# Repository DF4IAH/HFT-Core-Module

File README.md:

# HFT-Core-Module

## V1.1 PCB after placement was done:

## These are the included devices for the V1.1:
* __CPU: ST Microelectronics STM32L496ZGT6P__ (80MHz ARM Cortex-M4 w/ 1MB FLASH / 320kB RAM)
* __ext. Flash and EEPROM__ (8MB more data to be kept outside of the MCU / 8kB configuration data)
* __GSM / GNSS / BT: SIM868__ (SMS / GPRS / GPS, Glonass ...)
* __VHF/UHF FSK and LoRa: SX1262__ (VHF TX/RX)
* __VHF/UHF All but Lora: AX5243__ (VHF TX/RX)
* __Accel/Gyro/Mag: BNO085__ (3Axis-Acceleration, 3Axis-Gyro, 3Axis-Magneto - motion tracking engine)
* __Baro/Hygro/Temp/AirQuality: BME680__ (0.12Pa equiv. 1.7cm)
* __VCTCXO: CFPT-141_20MHz__ (being synchronized to the GPS 1PPS signal by pulling the VC)
* __Clock PLL__ (distributing any clocks that are needed)
* __Audio ADC and DAC__ (connected to the I2S facilities)
* __LCD 16x2 display__ (draws less than 1mA from the battery)
* __E-Ink-Display w/ 200x200px__ (more fun with even less energy)
* __Rotary encoder w/ pushbutton__ (Navigation of menues enabled)
* __Archer Headers__ (PCB expanded by up to two daughter boards)
* __SMA sockets: GSM, GNSS, BlueTooth, SX1262, AX5243__ (each device has its own antenna socket)
* __PMICs for 12V, USB, solar cells, 3.3V, 1.2V__ (high efficiency on board)
* __Electronic Switches: Subcircuits to be powered on/off by request__ (ultra-low-power to full-media)
* __LiPo-Connector: 1-cell 3.7V__ (high power request by the SIM868 device to be satisfied)
* __... and much fun with Free-RTOS...__ (Efficiency to the max  ;-)

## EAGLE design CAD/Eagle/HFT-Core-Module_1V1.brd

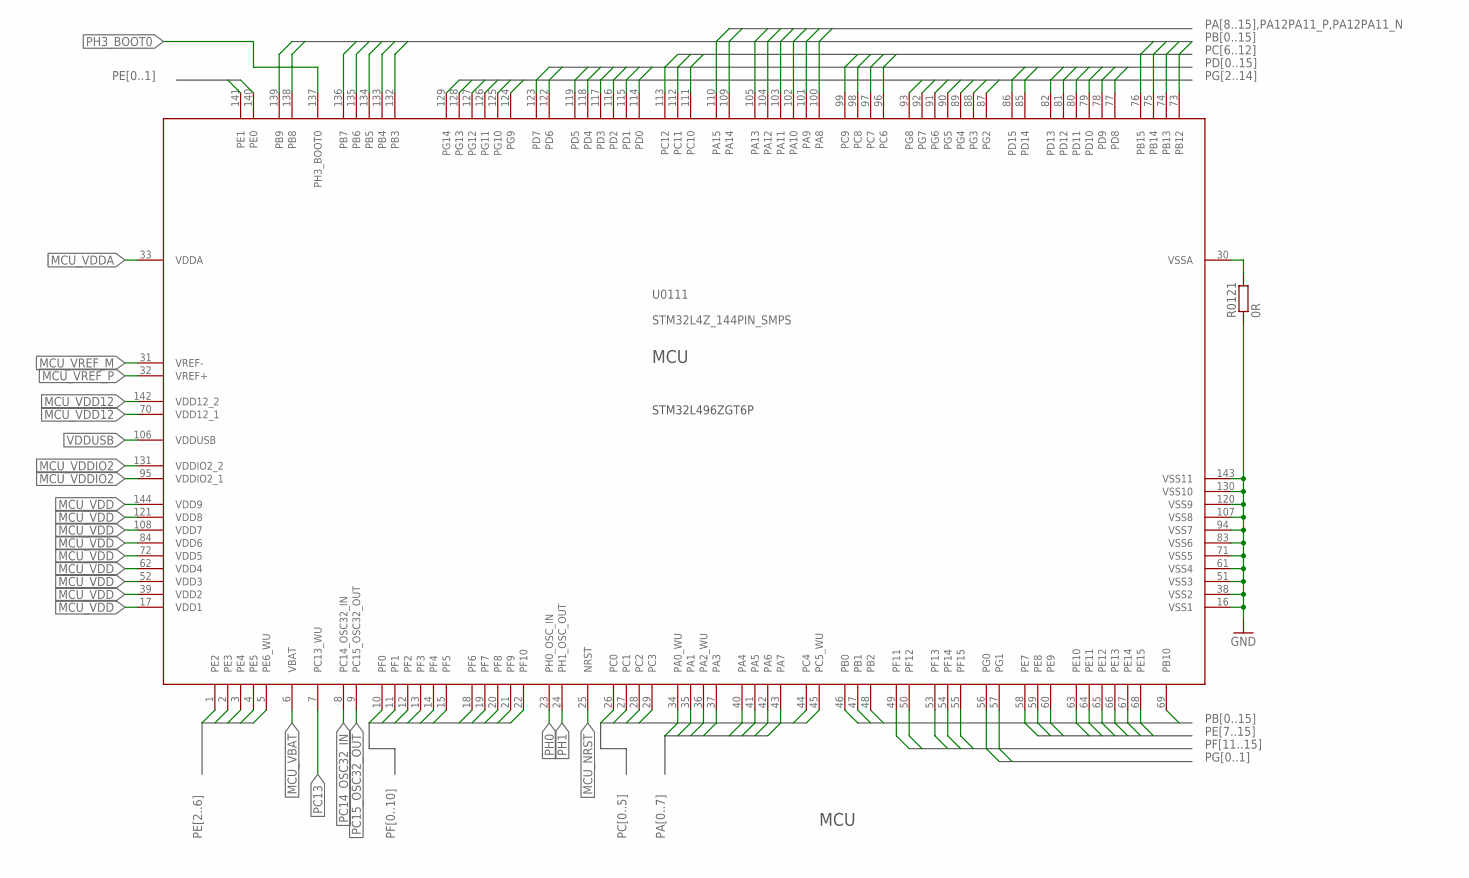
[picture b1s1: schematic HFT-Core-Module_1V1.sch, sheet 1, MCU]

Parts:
R0121: 0R; R0402
U0111: STM32L4Z_144PIN_SMPS; LQFP144

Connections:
GND: R0121.1, U0111.16 (VSS1), U0111.38 (VSS2), U0111.51 (VSS3), U0111.61 (VSS4), U0111.71 (VSS5), U0111.83 (VSS6), U0111.94 (VSS7), U0111.107 (VSS8), U0111.120 (VSS9), U0111.130 (VSS10), U0111.143 (VSS11); also elsewhere on the board
MCU_NRST: U0111.25 (NRST); also elsewhere on the board
MCU_VBAT: U0111.6 (VBAT); also elsewhere on the board
MCU_VDD: U0111.17 (VDD1), U0111.39 (VDD2), U0111.52 (VDD3), U0111.62 (VDD4), U0111.72 (VDD5), U0111.84 (VDD6), U0111.108 (VDD7), U0111.121 (VDD8), U0111.144 (VDD9); also elsewhere on the board
MCU_VDD12: U0111.70 (VDD12_1), U0111.142 (VDD12_2); also elsewhere on the board
MCU_VDDA: U0111.33 (VDDA); also elsewhere on the board
MCU_VDDIO2: U0111.95 (VDDIO2_1), U0111.131 (VDDIO2_2); also elsewhere on the board
MCU_VREF_M: U0111.31 (VREF-); also elsewhere on the board
MCU_VREF_P: U0111.32 (VREF+); also elsewhere on the board
MCU_VSSA: R0121.2, U0111.30 (VSSA)
PA0: U0111.34 (PA0_WU); also elsewhere on the board
PA1: U0111.35 (PA1); also elsewhere on the board
PA2: U0111.36 (PA2_WU); also elsewhere on the board
PA3: U0111.37 (PA3); also elsewhere on the board
PA4: U0111.40 (PA4)
PA5: U0111.41 (PA5); also elsewhere on the board
PA6: U0111.42 (PA6); also elsewhere on the board
PA7: U0111.43 (PA7); also elsewhere on the board
PA8: U0111.100 (PA8); also elsewhere on the board
PA9: U0111.101 (PA9); also elsewhere on the board
PA10: U0111.102 (PA10); also elsewhere on the board
PA12PA11_N: U0111.103 (PA11); also elsewhere on the board
PA12PA11_P: U0111.104 (PA12); also elsewhere on the board
PA13: U0111.105 (PA13); also elsewhere on the board
PA14: U0111.109 (PA14); also elsewhere on the board
PA15: U0111.110 (PA15)
PB0: U0111.46 (PB0); also elsewhere on the board
PB1: U0111.47 (PB1); also elsewhere on the board
PB2: U0111.48 (PB2)
PB3: U0111.132 (PB3); also elsewhere on the board
PB4: U0111.133 (PB4)
PB5: U0111.134 (PB5); also elsewhere on the board
PB6: U0111.135 (PB6); also elsewhere on the board
PB7: U0111.136 (PB7); also elsewhere on the board
PB8: U0111.138 (PB8)
PB9: U0111.139 (PB9)
PB10: U0111.69 (PB10)
PB12: U0111.73 (PB12)
PB13: U0111.74 (PB13); also elsewhere on the board
PB14: U0111.75 (PB14)
PB15: U0111.76 (PB15); also elsewhere on the board
PC0: U0111.26 (PC0); also elsewhere on the board
PC1: U0111.27 (PC1); also elsewhere on the board
PC2: U0111.28 (PC2); also elsewhere on the board
PC3: U0111.29 (PC3); also elsewhere on the board
PC4: U0111.44 (PC4)
PC5: U0111.45 (PC5_WU); also elsewhere on the board
PC6: U0111.96 (PC6); also elsewhere on the board
PC7: U0111.97 (PC7); also elsewhere on the board
PC8: U0111.98 (PC8); also elsewhere on the board
PC9: U0111.99 (PC9); also elsewhere on the board
PC10: U0111.111 (PC10); also elsewhere on the board
PC11: U0111.112 (PC11); also elsewhere on the board
PC12: U0111.113 (PC12); also elsewhere on the board
PC13: U0111.7 (PC13_WU); also elsewhere on the board
PC14_OSC32_IN: U0111.8 (PC14_OSC32_IN); also elsewhere on the board
PC15_OSC32_OUT: U0111.9 (PC15_OSC32_OUT); also elsewhere on the board
PD0: U0111.114 (PD0)
PD1: U0111.115 (PD1); also elsewhere on the board
PD2: U0111.116 (PD2); also elsewhere on the board
PD3: U0111.117 (PD3); also elsewhere on the board
PD4: U0111.118 (PD4)
PD5: U0111.119 (PD5)
PD6: U0111.122 (PD6)
PD7: U0111.123 (PD7); also elsewhere on the board
PD8: U0111.77 (PD8); also elsewhere on the board
PD9: U0111.78 (PD9); also elsewhere on the board
PD10: U0111.79 (PD10); also elsewhere on the board
PD11: U0111.80 (PD11); also elsewhere on the board
PD12: U0111.81 (PD12); also elsewhere on the board
PD13: U0111.82 (PD13)
PD14: U0111.85 (PD14); also elsewhere on the board
PD15: U0111.86 (PD15); also elsewhere on the board
PE0: U0111.140 (PE0)
PE1: U0111.141 (PE1)
PE2: U0111.1 (PE2)
PE3: U0111.2 (PE3); also elsewhere on the board
PE4: U0111.3 (PE4); also elsewhere on the board
PE5: U0111.4 (PE5); also elsewhere on the board
PE6: U0111.5 (PE6_WU); also elsewhere on the board
PE7: U0111.58 (PE7); also elsewhere on the board
PE8: U0111.59 (PE8); also elsewhere on the board
PE9: U0111.60 (PE9); also elsewhere on the board
PE10: U0111.63 (PE10); also elsewhere on the board
PE11: U0111.64 (PE11); also elsewhere on the board
PE12: U0111.65 (PE12); also elsewhere on the board
PE13: U0111.66 (PE13); also elsewhere on the board
PE14: U0111.67 (PE14); also elsewhere on the board
PE15: U0111.68 (PE15); also elsewhere on the board
PF0: U0111.10 (PF0); also elsewhere on the board
PF1: U0111.11 (PF1); also elsewhere on the board
PF2: U0111.12 (PF2)
PF3: U0111.13 (PF3); also elsewhere on the board
PF4: U0111.14 (PF4); also elsewhere on the board
PF5: U0111.15 (PF5); also elsewhere on the board
PF6: U0111.18 (PF6); also elsewhere on the board
PF7: U0111.19 (PF7); also elsewhere on the board
PF8: U0111.20 (PF8); also elsewhere on the board
PF9: U0111.21 (PF9); also elsewhere on the board
PF10: U0111.22 (PF10); also elsewhere on the board
PF11: U0111.49 (PF11); also elsewhere on the board
PF12: U0111.50 (PF12); also elsewhere on the board
PF13: U0111.53 (PF13); also elsewhere on the board
PF14: U0111.54 (PF14); also elsewhere on the board
PF15: U0111.55 (PF15); also elsewhere on the board
PG0: U0111.56 (PG0); also elsewhere on the board
PG1: U0111.57 (PG1); also elsewhere on the board
PG2: U0111.87 (PG2)
PG3: U0111.88 (PG3); also elsewhere on the board
PG4: U0111.89 (PG4); also elsewhere on the board
PG5: U0111.90 (PG5); also elsewhere on the board
PG6: U0111.91 (PG6); also elsewhere on the board
PG7: U0111.92 (PG7); also elsewhere on the board
PG8: U0111.93 (PG8); also elsewhere on the board
PG9: U0111.124 (PG9); also elsewhere on the board
PG10: U0111.125 (PG10); also elsewhere on the board
PG11: U0111.126 (PG11); also elsewhere on the board
PG12: U0111.127 (PG12); also elsewhere on the board
PG13: U0111.128 (PG13); also elsewhere on the board
PG14: U0111.129 (PG14); also elsewhere on the board
PH0: U0111.23 (PH0_OSC_IN); also elsewhere on the board
PH1: U0111.24 (PH1_OSC_OUT)
PH3_BOOT0: U0111.137 (PH3_BOOT0); also elsewhere on the board
VDDUSB: U0111.106 (VDDUSB); also elsewhere on the board

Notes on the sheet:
STM32L496ZGT6P
MCU

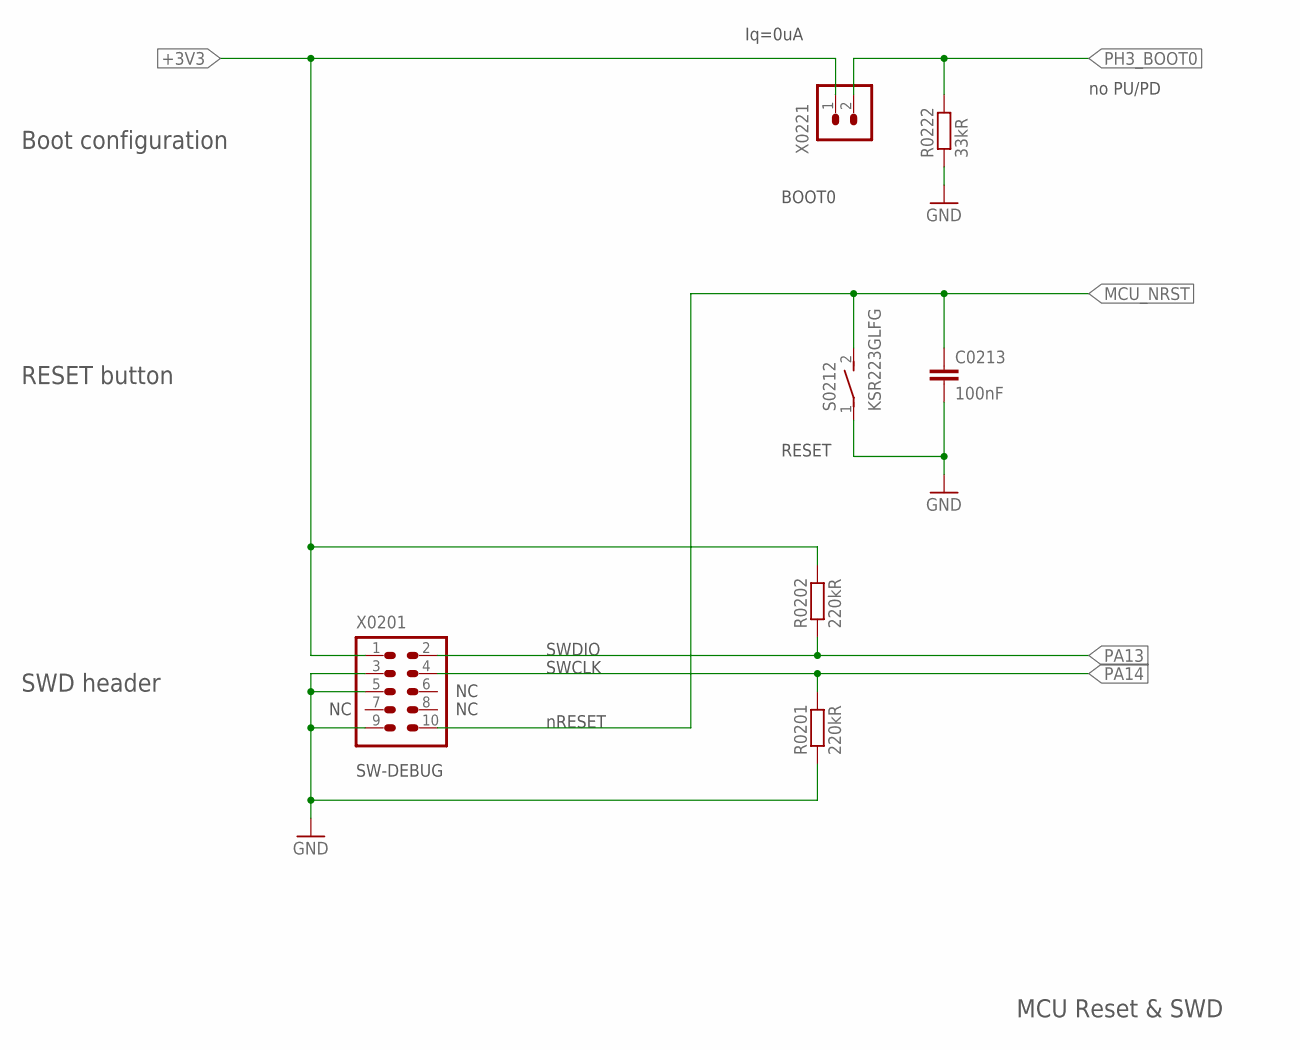
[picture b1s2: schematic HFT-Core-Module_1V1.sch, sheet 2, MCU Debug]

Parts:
C0213: 100nF; C0402
R0201, R0202: 220kR; R0402
R0222: 33kR; R0402
S0212: KSR223GLFG; KSR223G_SMD_1POL
X0201: 2X05_1MM27_SHROUDED_CORTEX_JTAG_SWD"; 2X05_1MM27_SHROUDED_CORTEX_JTAG_SWD
X0221: HEADER-1X2; 1X02

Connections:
+3V3: R0202.2, X0201.1, X0221.1; also elsewhere on the board
GND: C0213.2, R0201.1, R0222.1, S0212.1, X0201.3, X0201.5, X0201.9; also elsewhere on the board
MCU_NRST: C0213.1, S0212.2 (S), X0201.10; also elsewhere on the board
PA13: R0202.1, X0201.2; also elsewhere on the board
PA14: R0201.2, X0201.4; also elsewhere on the board
PH3_BOOT0: R0222.2, X0221.2; also elsewhere on the board

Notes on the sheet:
SWDIO
SWCLK
RESET
BOOT0
SW-DEBUG
SWD header
Boot configuration
RESET button
nRESET
MCU Reset & SWD
no PU/PD
Iq=0uA

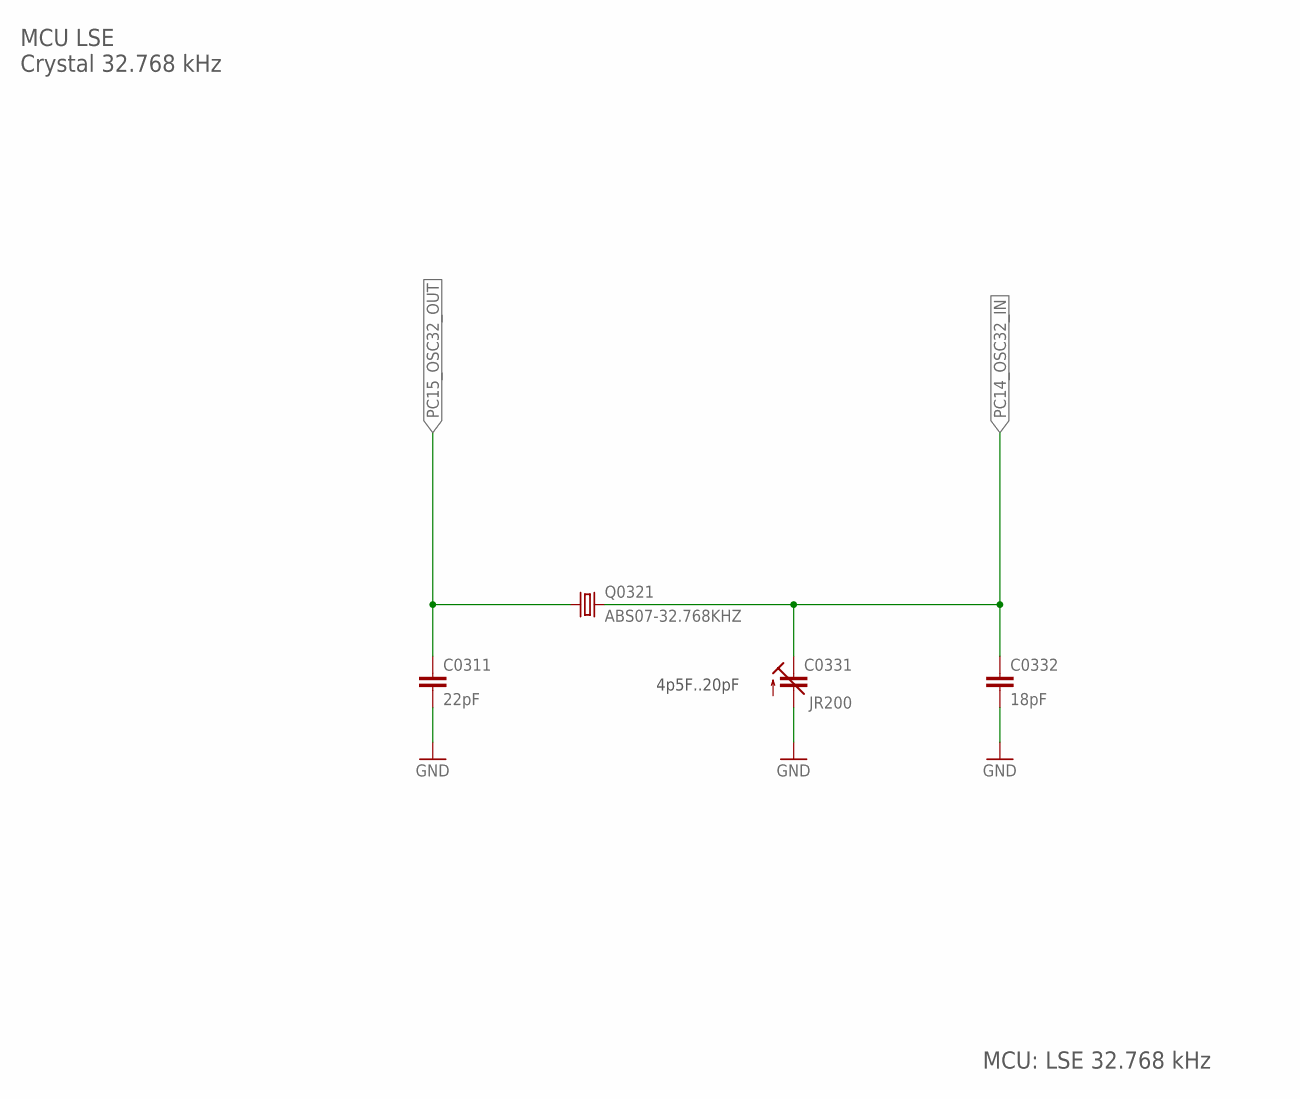
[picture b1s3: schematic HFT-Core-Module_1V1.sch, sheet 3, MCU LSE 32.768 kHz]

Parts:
C0311: 22pF; C0402
C0331: JR200; 3MM2_X_2MM5
C0332: 18pF; C0402
Q0321: ABS07-32.768KHZ; ABS07

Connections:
GND: C0311.2, C0331.+ (A), C0332.2; also elsewhere on the board
PC14_OSC32_IN: C0331.- (E), C0332.1, Q0321.2; also elsewhere on the board
PC15_OSC32_OUT: C0311.1, Q0321.1; also elsewhere on the board

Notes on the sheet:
4p5F..20pF
MCU LSE Crystal 32.768 kHz
MCU: LSE 32.768 kHz

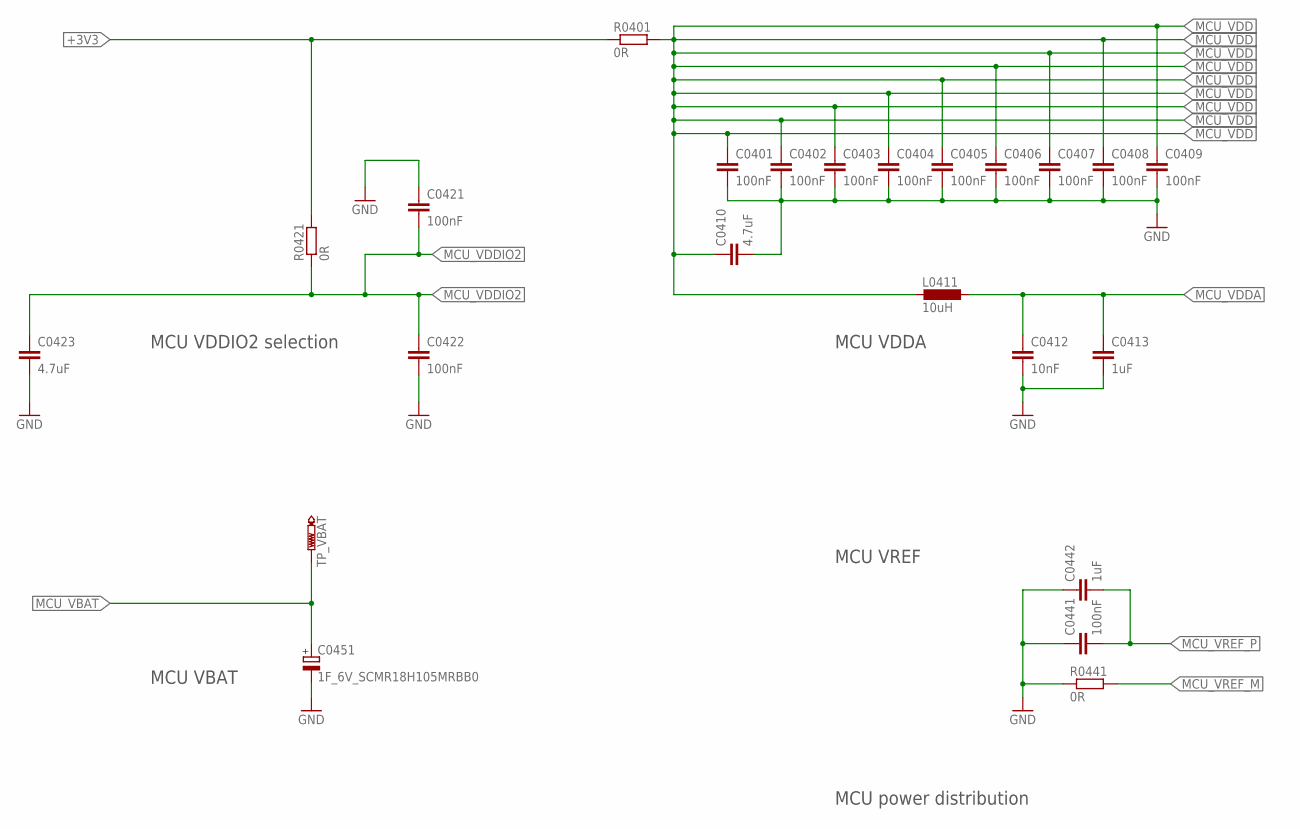
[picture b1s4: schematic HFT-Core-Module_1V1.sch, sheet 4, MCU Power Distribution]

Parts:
C0401, C0402, C0403, C0404, C0405, C0406, C0407, C0408, C0409, C0421, C0422, C0441: 100nF; C0402
C0410, C0423: 4.7uF; C0402
C0412: 10nF; C0402
C0413, C0442: 1uF; C0402
C0451: 1F_6V_SCMR18H105MRBB0; C115-080X160_POL
L0411: 10uH; L0603
R0401, R0421, R0441: 0R; R0402
TP_VBAT: PTR1B1,27; B1,27

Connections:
+3V3: R0401.1, R0421.2; also elsewhere on the board
GND: C0401.2, C0402.2, C0403.2, C0404.2, C0405.2, C0406.2, C0407.2, C0408.2, C0409.2, C0410.2, C0412.2, C0413.2, C0421.1, C0422.2, C0423.2, C0441.1, C0442.1, C0451.-, R0441.1; also elsewhere on the board
MCU_VBAT: C0451.+, TP_VBAT.TP; also elsewhere on the board
MCU_VDD: C0401.1, C0402.1, C0403.1, C0404.1, C0405.1, C0406.1, C0407.1, C0408.1, C0409.1, C0410.1, L0411.1, R0401.2; also elsewhere on the board
MCU_VDDA: C0412.1, C0413.1, L0411.2; also elsewhere on the board
MCU_VDDIO2: C0421.2, C0422.1, C0423.1, R0421.1; also elsewhere on the board
MCU_VREF_M: R0441.2; also elsewhere on the board
MCU_VREF_P: C0441.2, C0442.2; also elsewhere on the board

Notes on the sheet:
MCU VDDIO2 selection
MCU VDDA
MCU VREF
MCU VBAT
MCU power distribution

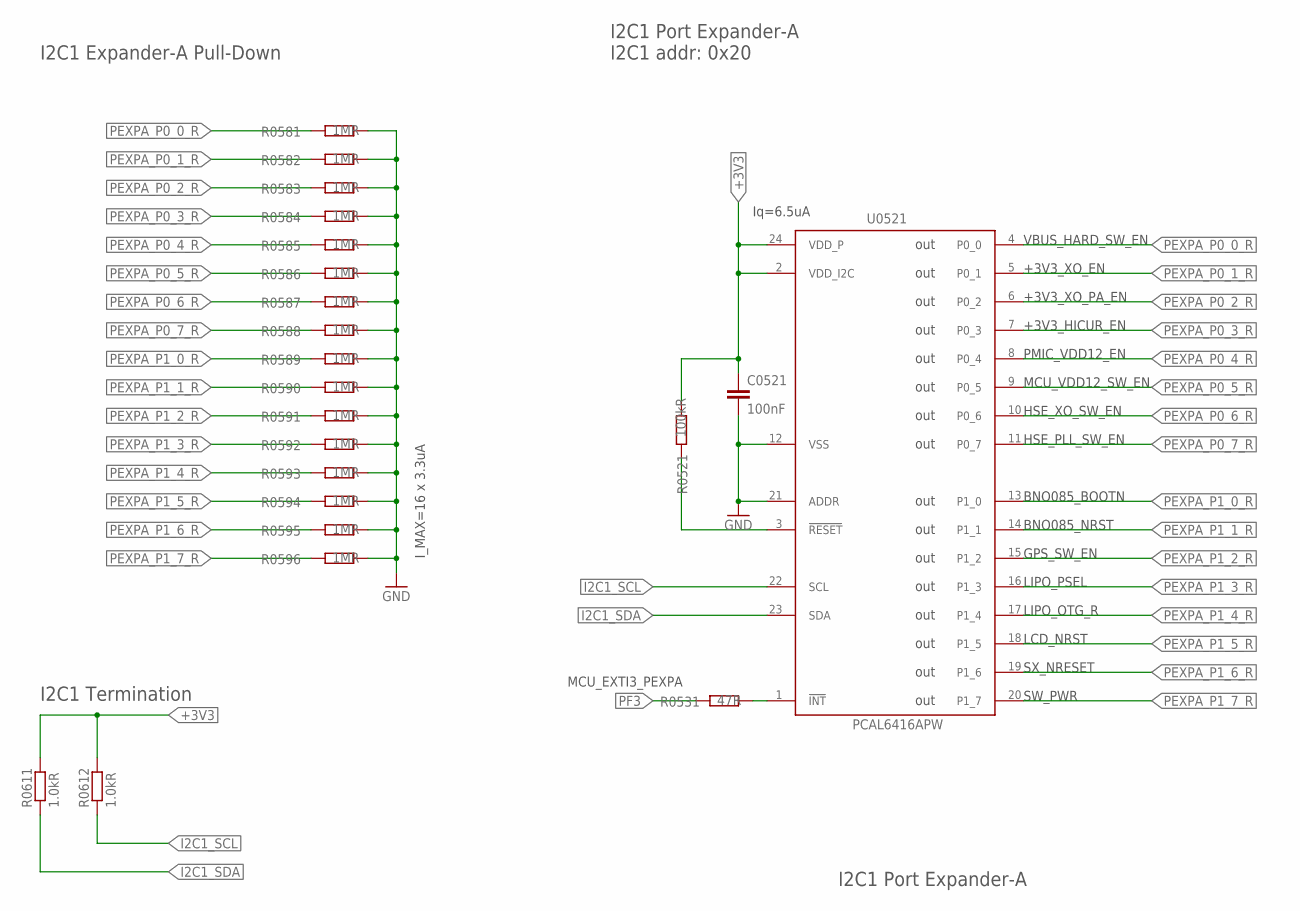
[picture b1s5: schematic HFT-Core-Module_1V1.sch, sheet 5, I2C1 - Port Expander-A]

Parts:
C0521: 100nF; C0402
R0521: 100kR; R0402
R0531: 47R; R0402
R0581, R0582, R0583, R0584, R0585, R0586, R0587, R0588, R0589, R0590, R0591, R0592, R0593, R0594, R0595, R0596: 1MR; R0402
R0611, R0612: 1.0kR; R0402
U0521: PCAL6416APW; TSSOP24_SOT355-1

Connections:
+3V3: C0521.1, R0521.2, R0611.2, R0612.2, U0521.2 (VDD_I2C), U0521.24 (VDD_P); also elsewhere on the board
GND: C0521.2, R0581.2, R0582.2, R0583.2, R0584.2, R0585.2, R0586.2, R0587.2, R0588.2, R0589.2, R0590.2, R0591.2, R0592.2, R0593.2, R0594.2, R0595.2, R0596.2, U0521.12 (VSS), U0521.21 (ADDR); also elsewhere on the board
I2C1_SCL: R0612.1, U0521.22 (SCL); also elsewhere on the board
I2C1_SDA: R0611.1, U0521.23 (SDA); also elsewhere on the board
PEXPA_INTN: R0531.2, U0521.1 (!INT)
PEXPA_P0_0_R: R0581.1, U0521.4 (P0_0); also elsewhere on the board
PEXPA_P0_1_R: R0582.1, U0521.5 (P0_1); also elsewhere on the board
PEXPA_P0_2_R: R0583.1, U0521.6 (P0_2); also elsewhere on the board
PEXPA_P0_3_R: R0584.1, U0521.7 (P0_3); also elsewhere on the board
PEXPA_P0_4_R: R0585.1, U0521.8 (P0_4); also elsewhere on the board
PEXPA_P0_5_R: R0586.1, U0521.9 (P0_5); also elsewhere on the board
PEXPA_P0_6_R: R0587.1, U0521.10 (P0_6); also elsewhere on the board
PEXPA_P0_7_R: R0588.1, U0521.11 (P0_7); also elsewhere on the board
PEXPA_P1_0_R: R0589.1, U0521.13 (P1_0); also elsewhere on the board
PEXPA_P1_1_R: R0590.1, U0521.14 (P1_1); also elsewhere on the board
PEXPA_P1_2_R: R0591.1, U0521.15 (P1_2); also elsewhere on the board
PEXPA_P1_3_R: R0592.1, U0521.16 (P1_3); also elsewhere on the board
PEXPA_P1_4_R: R0593.1, U0521.17 (P1_4); also elsewhere on the board
PEXPA_P1_5_R: R0594.1, U0521.18 (P1_5); also elsewhere on the board
PEXPA_P1_6_R: R0595.1, U0521.19 (P1_6); also elsewhere on the board
PEXPA_P1_7_R: R0596.1, U0521.20 (P1_7); also elsewhere on the board
PEXPA_RESET: R0521.1, U0521.3 (!RESET)
PF3: R0531.1; also elsewhere on the board

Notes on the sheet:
I2C1 Port Expander-A I2C1 addr: 0x20
I2C1 Expander-A Pull-Down
I2C1 Port Expander-A
Iq=6.5uA
I_MAX=16 x 3.3uA
MCU_EXTI3_PEXPA
VBUS_HARD_SW_EN
+3V3_XO_EN
+3V3_XO_PA_EN
+3V3_HICUR_EN
PMIC_VDD12_EN
MCU_VDD12_SW_EN
HSE_XO_SW_EN
HSE_PLL_SW_EN
BNO085_BOOTN
BNO085_NRST
GPS_SW_EN
LIPO_PSEL
LIPO_OTG_R
SX_NRESET
LCD_NRST
SW_PWR
out
I2C1 Termination

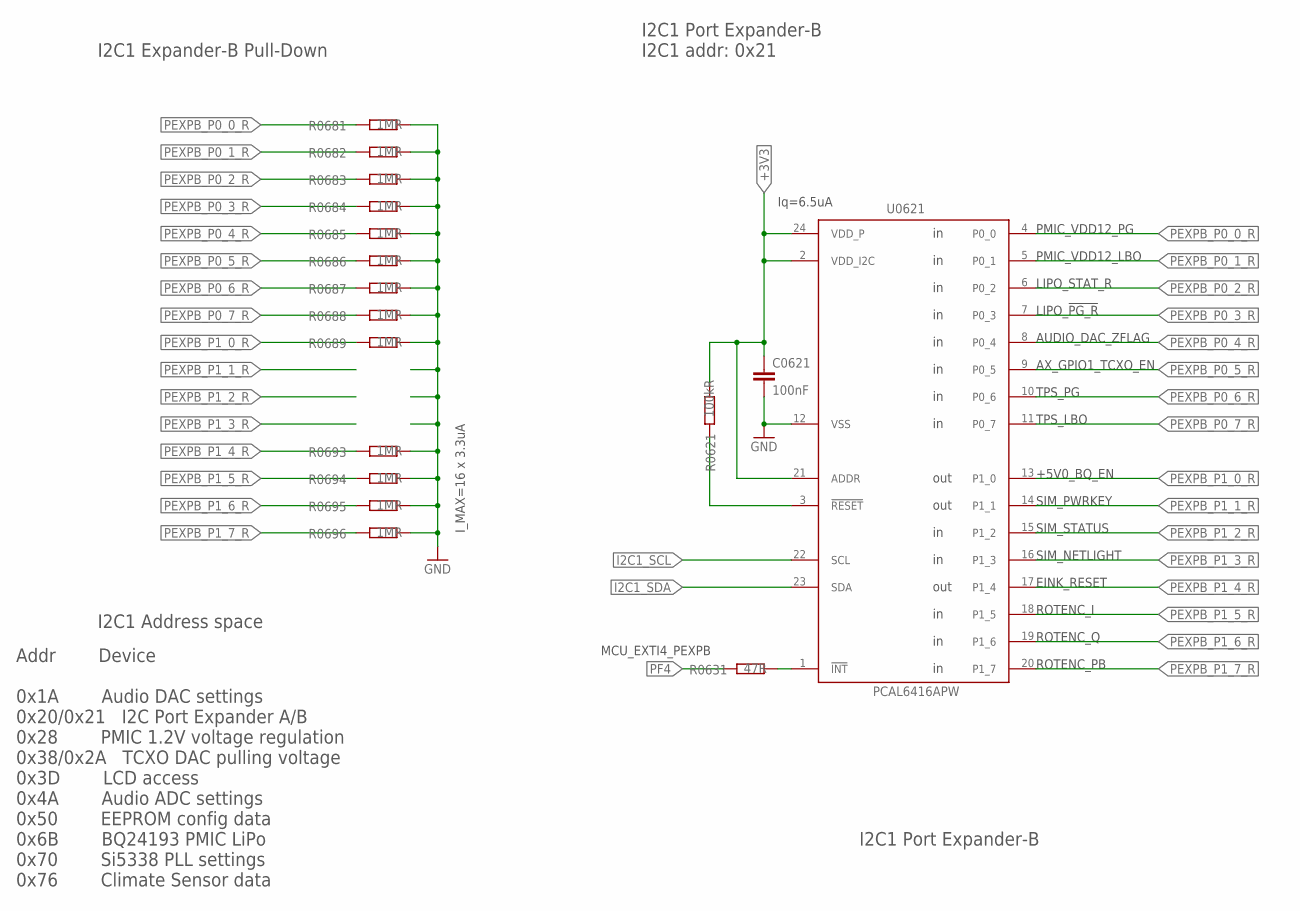
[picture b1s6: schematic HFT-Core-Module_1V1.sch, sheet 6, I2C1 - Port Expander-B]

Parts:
C0621: 100nF; C0402
R0621: 100kR; R0402
R0631: 47R; R0402
R0681, R0682, R0683, R0684, R0685, R0686, R0687, R0688, R0689, R0693, R0694, R0695, R0696: 1MR; R0402
U0621: PCAL6416APW; TSSOP24_SOT355-1

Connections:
+3V3: C0621.1, R0621.2, U0621.2 (VDD_I2C), U0621.21 (ADDR), U0621.24 (VDD_P); also elsewhere on the board
GND: C0621.2, R0681.2, R0682.2, R0683.2, R0684.2, R0685.2, R0686.2, R0687.2, R0688.2, R0689.2, R0693.2, R0694.2, R0695.2, R0696.2, U0621.12 (VSS); also elsewhere on the board
I2C1_SCL: U0621.22 (SCL); also elsewhere on the board
I2C1_SDA: U0621.23 (SDA); also elsewhere on the board
PEXPB_INTN: R0631.2, U0621.1 (!INT)
PEXPB_P0_0_R: R0681.1, U0621.4 (P0_0)
PEXPB_P0_1_R: R0682.1, U0621.5 (P0_1)
PEXPB_P0_2_R: R0683.1, U0621.6 (P0_2); also elsewhere on the board
PEXPB_P0_3_R: R0684.1, U0621.7 (P0_3); also elsewhere on the board
PEXPB_P0_4_R: R0685.1, U0621.8 (P0_4); also elsewhere on the board
PEXPB_P0_5_R: R0686.1, U0621.9 (P0_5); also elsewhere on the board
PEXPB_P0_6_R: R0687.1, U0621.10 (P0_6)
PEXPB_P0_7_R: R0688.1, U0621.11 (P0_7)
PEXPB_P1_0_R: R0689.1, U0621.13 (P1_0); also elsewhere on the board
PEXPB_P1_1_R: U0621.14 (P1_1); also elsewhere on the board
PEXPB_P1_2_R: U0621.15 (P1_2); also elsewhere on the board
PEXPB_P1_3_R: U0621.16 (P1_3); also elsewhere on the board
PEXPB_P1_4_R: R0693.1, U0621.17 (P1_4); also elsewhere on the board
PEXPB_P1_5_R: R0694.1, U0621.18 (P1_5); also elsewhere on the board
PEXPB_P1_6_R: R0695.1, U0621.19 (P1_6); also elsewhere on the board
PEXPB_P1_7_R: R0696.1, U0621.20 (P1_7); also elsewhere on the board
PEXPB_RESET: R0621.1, U0621.3 (!RESET)
PF4: R0631.1; also elsewhere on the board

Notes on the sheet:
Addr Device 0x1A Audio DAC settings 0x20/0x21 I2C Port Expander A/B 0x28 PMIC 1.2V voltage regulation 0x38/0x2A TCXO DAC pulling voltage 0x3D LCD access 0x4A Audio ADC settings 0x50 EEPROM config data 0x6B BQ24193 PMIC LiPo 0x70 Si5338 PLL settings 0x76 Climate Sensor data
I2C1 Port Expander-B
I2C1 Address space
I2C1 Port Expander-B I2C1 addr: 0x21
I2C1 Expander-B Pull-Down
Iq=6.5uA
I_MAX=16 x 3.3uA
MCU_EXTI4_PEXPB
SIM_STATUS
SIM_NETLIGHT
+5V0_BQ_EN
ROTENC_I
ROTENC_Q
ROTENC_PB
AX_GPIO1_TCXO_EN
PMIC_VDD12_PG
PMIC_VDD12_LBO
LIPO_STAT_R
LIPO_!PG_R
AUDIO_DAC_ZFLAG
SIM_PWRKEY
out
EINK_RESET
TPS_PG
TPS_LBO

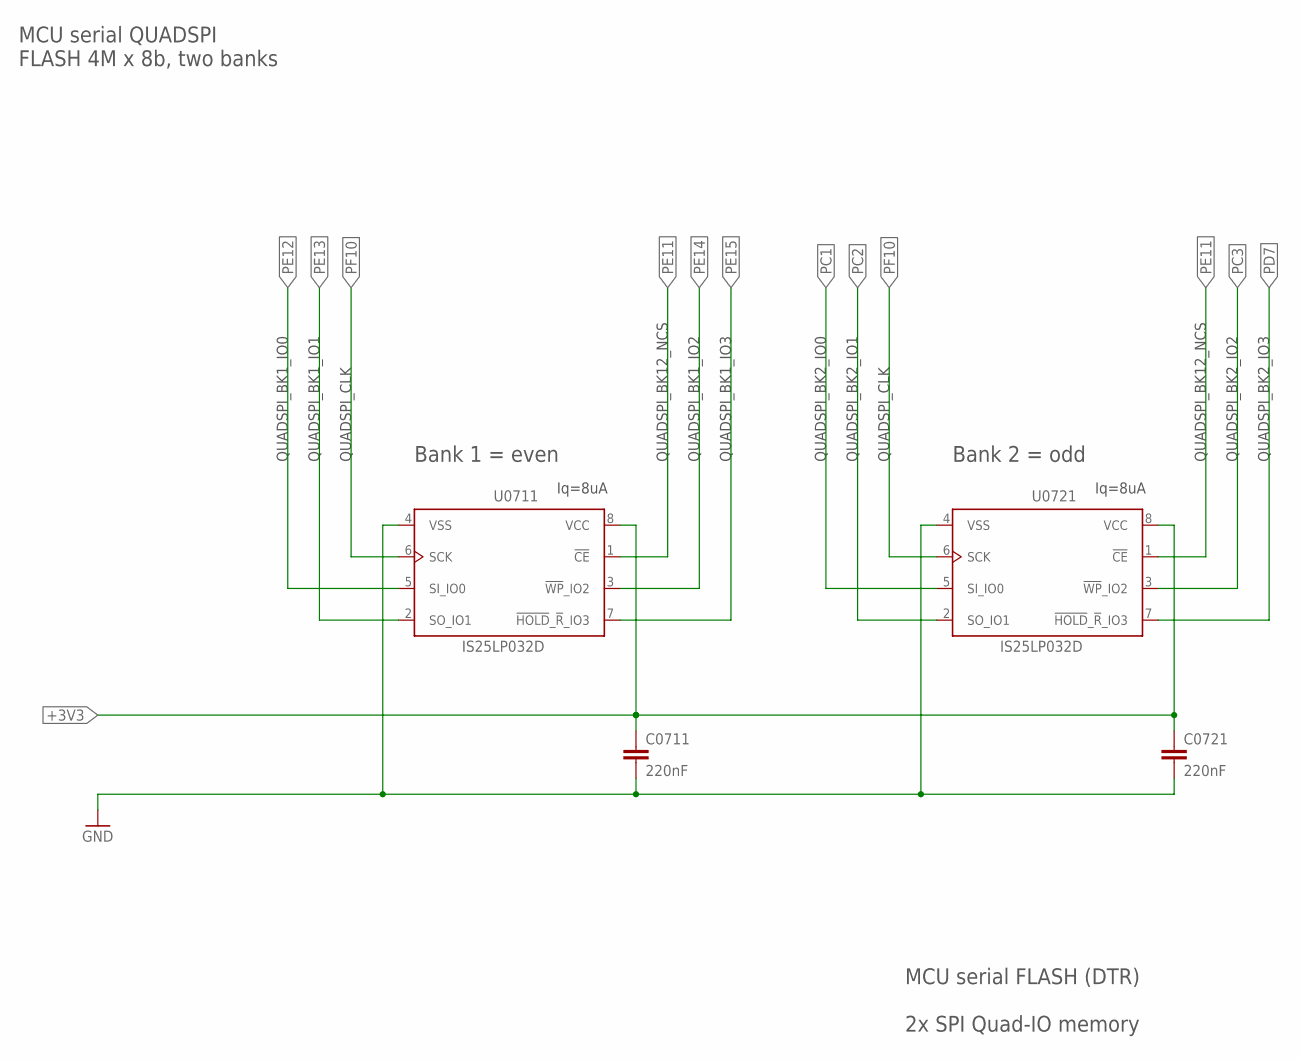
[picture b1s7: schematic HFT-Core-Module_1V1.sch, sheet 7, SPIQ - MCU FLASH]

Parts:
C0711, C0721: 220nF; C0402
U0711, U0721: IS25LP032D; SOIC8_150MIL

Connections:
+3V3: C0711.1, C0721.1, U0711.8 (VCC), U0721.8 (VCC); also elsewhere on the board
GND: C0711.2, C0721.2, U0711.4 (VSS), U0721.4 (VSS); also elsewhere on the board
PC1: U0721.5 (SI_IO0); also elsewhere on the board
PC2: U0721.2 (SO_IO1); also elsewhere on the board
PC3: U0721.3 (!WP!_IO2); also elsewhere on the board
PD7: U0721.7 (!HOLD!_!R!_IO3); also elsewhere on the board
PE11: U0711.1 (!CE), U0721.1 (!CE); also elsewhere on the board
PE12: U0711.5 (SI_IO0); also elsewhere on the board
PE13: U0711.2 (SO_IO1); also elsewhere on the board
PE14: U0711.3 (!WP!_IO2); also elsewhere on the board
PE15: U0711.7 (!HOLD!_!R!_IO3); also elsewhere on the board
PF10: U0711.6 (SCK), U0721.6 (SCK); also elsewhere on the board

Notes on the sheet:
QUADSPI_CLK
QUADSPI_BK2_IO0
QUADSPI_BK2_IO1
QUADSPI_BK2_IO2
QUADSPI_BK2_IO3
QUADSPI_BK12_NCS
QUADSPI_BK1_IO0
QUADSPI_BK1_IO1
QUADSPI_BK1_IO2
QUADSPI_BK1_IO3
MCU serial QUADSPI FLASH 4M x 8b, two banks
MCU serial FLASH (DTR) 2x SPI Quad-IO memory
Bank 1 = even
Bank 2 = odd
Iq=8uA

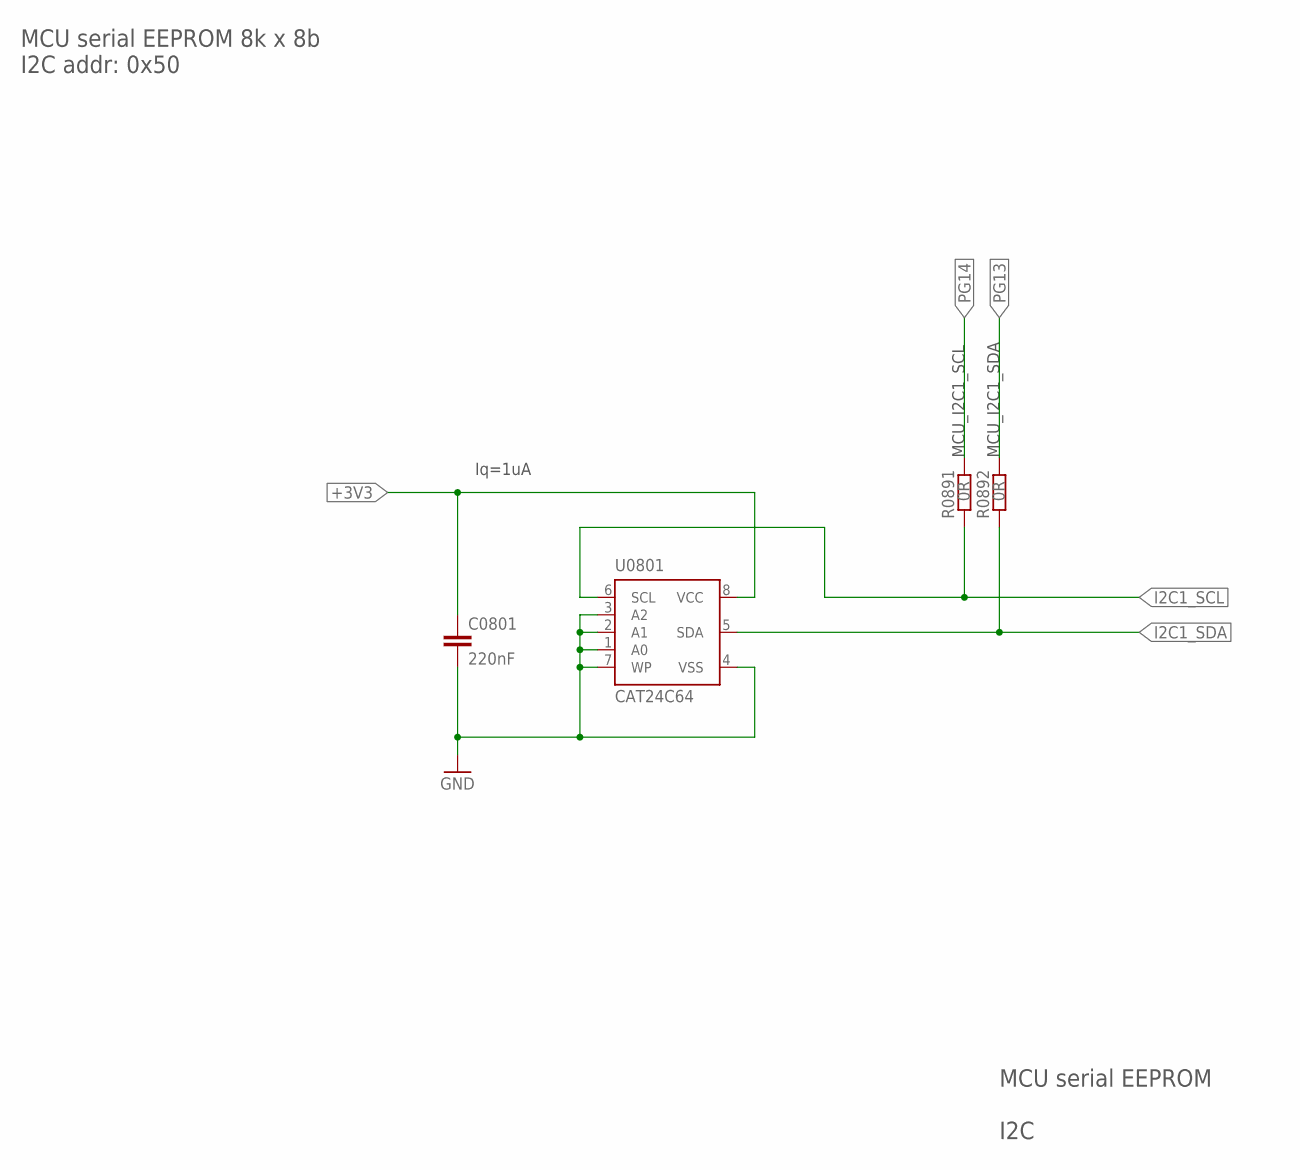
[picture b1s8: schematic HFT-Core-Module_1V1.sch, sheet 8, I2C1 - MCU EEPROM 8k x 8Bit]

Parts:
C0801: 220nF; C0402
R0891, R0892: 0R; R0402
U0801: CAT24C64; SOIC8_150MIL

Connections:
+3V3: C0801.1, U0801.8 (VCC); also elsewhere on the board
GND: C0801.2, U0801.1 (A0), U0801.2 (A1), U0801.3 (A2), U0801.4 (VSS), U0801.7 (WP); also elsewhere on the board
I2C1_SCL: R0891.1, U0801.6 (SCL); also elsewhere on the board
I2C1_SDA: R0892.1, U0801.5 (SDA); also elsewhere on the board
PG13: R0892.2; also elsewhere on the board
PG14: R0891.2; also elsewhere on the board

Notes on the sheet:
MCU serial EEPROM I2C
MCU serial EEPROM 8k x 8b I2C addr: 0x50
MCU_I2C1_SCL
MCU_I2C1_SDA
Iq=1uA

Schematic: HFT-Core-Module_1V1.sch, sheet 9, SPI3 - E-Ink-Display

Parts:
C0901: 100nF; C0402
R0901, R0902, R0903, R0904, R0905, R0906: 47R; R0402
U0911: ZIO_EINK_1IN54

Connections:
+3V3: C0901.1, U0911.1 (EINK_VDD); also elsewhere on the board
EINK_BUSY_R: R0906.2, U0911.8 (EINK_BUSY)
EINK_CS_R: R0903.2, U0911.5 (EINK_CS)
EINK_D/C_R: R0904.2, U0911.6 (EINK_D/C)
EINK_RESET_R: R0905.2, U0911.7 (EINK_RES)
GND: C0901.2, U0911.2 (EINK_GND), U0911.9 (EINK_BS); also elsewhere on the board
MCU_SPI3_MOSI: R0901.2, U0911.3 (EINK_MOSI); also elsewhere on the board
MCU_SPI3_SCK: R0902.2, U0911.4 (EINK_SCK); also elsewhere on the board
PC8: R0906.1; also elsewhere on the board
PC10: R0902.1; also elsewhere on the board
PC12: R0901.1; also elsewhere on the board
PEXPB_P1_4_R: R0905.1; also elsewhere on the board
PG3: R0903.1; also elsewhere on the board
PG5: R0904.1; also elsewhere on the board

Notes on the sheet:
E-Ink Display
EINK_RESET
MCU_EINK_SEL_OUT
MCU_EINK_DC_OUT
MCU_EINK_BUSY_IN
MCU_SPI3_MOSI
MCU_SPI3_SCK
MCU_SPI3_MOSI_OUT
MCU_SPI3_SCK_OUT

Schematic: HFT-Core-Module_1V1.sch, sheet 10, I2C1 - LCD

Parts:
C1001: 100nF; C0402
C1011, C1012: 1uF; C0402
R1031: 220kR; R0402
R1051: 1.5kR; R0402
R1052: 2.0kR; R0402
R1053: 27R; R0402
T1051: MMBT2222; SOT23
U1001: MIDAS_MCCOG21605B6W-FPTLWI

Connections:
+3V3: C1001.1, U1001.4 (VDD), U1001.12 (A_BL); also elsewhere on the board
GND: C1001.2, C1012.2, R1031.1, R1051.1, R1053.1, U1001.5 (VSS); also elsewhere on the board
I2C1_SCL: U1001.7 (SCL); also elsewhere on the board
I2C1_SDA: U1001.6 (SDA); also elsewhere on the board
LCD_BL_K: T1051.3 (C), U1001.11 (K_BL)
LCD_CAP1N: C1011.2, U1001.2 (CAP1N)
LCD_CAP1P: C1011.1, U1001.3 (CAP1P)
LCD_VOUT: C1012.1, U1001.1 (VOUT)
LED_B_B: R1051.2, R1052.1, T1051.1 (B)
LED_B_E: R1053.2, T1051.2 (E)
PE6: R1052.2; also elsewhere on the board
PEXPA_P1_5_R: R1031.2, U1001.8 (RST); also elsewhere on the board

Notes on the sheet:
LCD-Module I2C addr: 0x3D
MCU_PWM_LCD_BL
16x2 char LCD
LCD_NRST
Iq=0.17mA

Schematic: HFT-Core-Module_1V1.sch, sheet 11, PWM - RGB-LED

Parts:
C1101: 100nF; C0402
D1101: ASMT-YTB7-0AA02_RGB; ASMT-YTB7_0AA02_RGB
R1111, R1121, R1131: 1.5kR; R0402
R1112, R1122, R1132: 2.0kR; R0402
R1113, R1123, R1133: 27R; R0805
T1111, T1121, T1131: MMBT2222; SOT23

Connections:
+3V3: C1101.1, D1101.4 (RA), D1101.5 (GA), D1101.6 (BA); also elsewhere on the board
GND: C1101.2, R1111.1, R1113.1, R1121.1, R1123.1, R1131.1, R1133.1; also elsewhere on the board
LED_B_B1: R1131.2, R1132.1, T1131.1 (B)
LED_B_E1: R1133.2, T1131.2 (E)
LED_B_K1: D1101.1 (BC), T1131.3 (C)
LED_G_B1: R1121.2, R1122.1, T1121.1 (B)
LED_G_E1: R1123.2, T1121.2 (E)
LED_G_K1: D1101.2 (GC), T1121.3 (C)
LED_R_B1: R1111.2, R1112.1, T1111.1 (B)
LED_R_E1: R1113.2, T1111.2 (E)
LED_R_K1: D1101.3 (RC), T1111.3 (C)
PA7: R1122.2; also elsewhere on the board
PB0: R1132.2; also elsewhere on the board
PC6: R1112.2; also elsewhere on the board

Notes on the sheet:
RGB-LED PWM driven
MCU_PWM_LED_R
MCU_PWM_LED_G
MCU_PWM_LED_B
RGB - LED

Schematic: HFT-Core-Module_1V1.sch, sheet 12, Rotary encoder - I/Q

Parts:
C1201, C1202, C1203: 1nF; C0402
X1201: TTE_EN11-HSM

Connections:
GND: C1201.2, C1202.2, C1203.2, X1201.C, X1201.D; also elsewhere on the board
PEXPB_P1_5_R: C1201.1, X1201.A; also elsewhere on the board
PEXPB_P1_6_R: C1202.1, X1201.B; also elsewhere on the board
PEXPB_P1_7_R: C1203.1, X1201.E; also elsewhere on the board

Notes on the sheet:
Rotary Encoder with Pushbutton
ROTENC_I
ROTENC_Q
ROTENC_PB
Rotary encoder

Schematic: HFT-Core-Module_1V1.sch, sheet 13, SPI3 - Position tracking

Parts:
C1301, C1302, C1303: 100nF; C0402
C1321, C1322: 22pF; C0402
Q1321: ABS07-32.768KHZ; ABS07
R1301, R1302, R1303, R1304: 47R; R0402
R1331, R1332: 2kR; R0402
U1301: BNO085; BNO085_LGA28

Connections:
+3V3: C1301.1, C1302.1, R1331.2, R1332.2, U1301.3 (VDD), U1301.5 (PS1), U1301.28 (VDDIO); also elsewhere on the board
BNO085_CAP: C1303.1, U1301.9 (CAP)
BNO085_CLKSEL1_XOUT32: C1322.1, Q1321.1, U1301.26 (CLKSEL1/XOUT32)
BNO085_ENV_SCL: R1332.1, U1301.15 (ENV_SCL)
BNO085_ENV_SDA: R1331.1, U1301.16 (ENV_SDA)
BNO085_H_CSN: R1304.2, U1301.18 (H_CSN)
BNO085_INTN: R1302.2, U1301.14 (H_INTN)
BNO085_MISO: R1301.2, U1301.20 (H_SDA/MISO/TX)
BNO085_PS0_WAKE: R1303.2, U1301.6 (PS0/WAKE)
BNO085_XIN32: C1321.1, Q1321.2, U1301.27 (XIN32)
GND: C1301.2, C1302.2, C1303.2, C1321.2, C1322.2, U1301.2 (VSS), U1301.10 (CLKSEL0), U1301.25 (VSSIO); also elsewhere on the board
MCU_SPI3_MOSI: U1301.17 (SA0/H_MOSI); also elsewhere on the board
MCU_SPI3_SCK: U1301.19 (H_SCL/SCL/RX); also elsewhere on the board
PC5: R1303.1; also elsewhere on the board
PC11: R1301.1; also elsewhere on the board
PEXPA_P1_0_R: U1301.4 (BOOTN); also elsewhere on the board
PEXPA_P1_1_R: U1301.11 (NRST); also elsewhere on the board
PF11: R1304.1; also elsewhere on the board
PF13: R1302.1; also elsewhere on the board

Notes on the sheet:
9-axis sensor: BNO-085 SPI
MCU_EXTI13_BNO085
Position tracking
MCU_SPI3_MISO
BNO085_BOOTN
MCU_BNO085_PS0_WAKE_OUT
BNO085_NRST
MCU_BNO085_SEL_OUT
Iq=0.13mA

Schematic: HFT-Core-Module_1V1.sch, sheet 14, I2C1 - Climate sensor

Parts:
C1401: 100nF; C0402
U1401: BME680

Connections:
+3V3: C1401.1, U1401.2 (CSB), U1401.6 (VDDIO), U1401.8 (VDD); also elsewhere on the board
GND: C1401.2, U1401.1 (VSS), U1401.5 (SDO), U1401.7 (VSS); also elsewhere on the board
I2C1_SCL: U1401.4 (SCL_SCLK); also elsewhere on the board
I2C1_SDA: U1401.3 (SDI_SDA); also elsewhere on the board

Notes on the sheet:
Climate sensor: BME680 I2C addr: 0x76
Climate sensor
Iq=0.15uA

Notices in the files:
CAD/Eagle/Extensions/HFT-ArduinoShield-Module_1V0.brd:
(C) 2018 by HFT-Institut,
Hochschule Mannheim, Germany
CAD/Eagle/HFT-Core-Module_1V1.brd:
(C) 2019 by Fakultät N,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
CAD/Eagle/HFT_VHF-UHF-TRX_1V0.brd:
(c) 2018  Hochschule Mannheim
